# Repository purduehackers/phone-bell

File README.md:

# Phone Bell

A tool to turn a Western Electric rotary phone into a doorbell for Hack Night

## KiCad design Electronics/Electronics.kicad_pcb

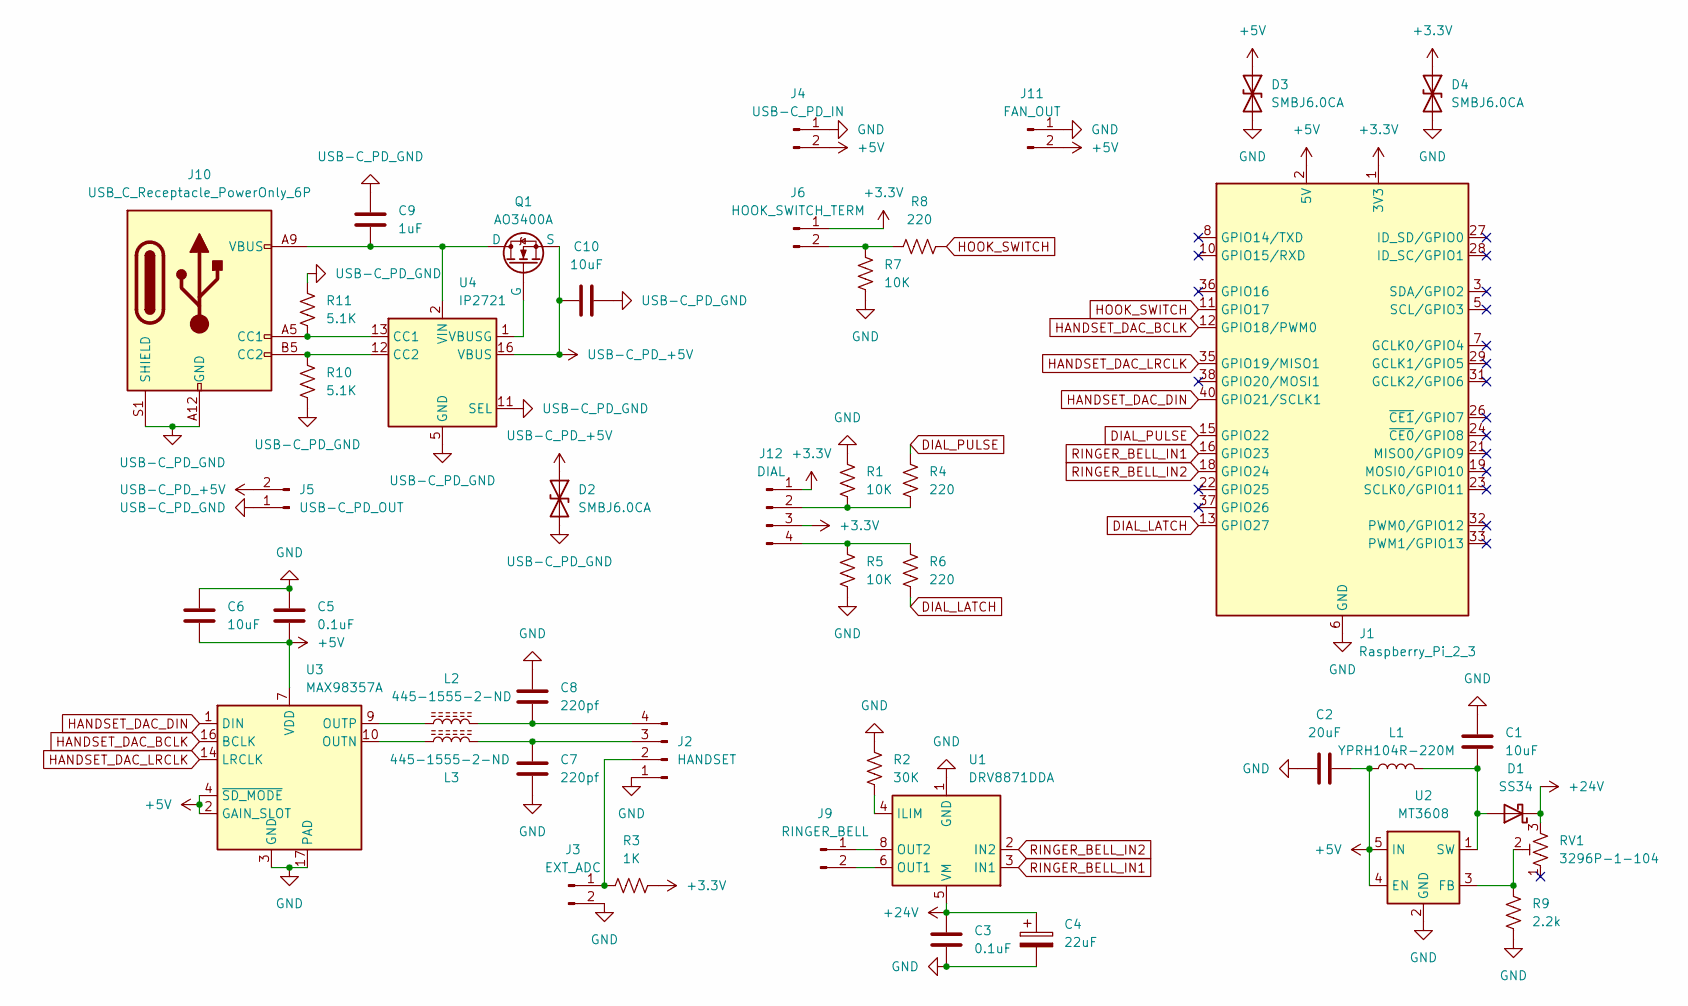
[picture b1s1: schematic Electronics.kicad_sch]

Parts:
C1, C6, C10: 10uF; C_0603_1608Metric
C2: 20uF; C_0603_1608Metric
C3, C5: 0.1uF; C_0603_1608Metric
C4: 22uF; C_0603_1608Metric
C7, C8: 220pf; C_0603_1608Metric
C9: 1uF; C_0603_1608Metric
D1: SS34; D_SMA
D2, D3, D4: SMBJ6.0CA; D_SMB
J1: Raspberry_Pi_2_3; PinSocket_2x20_P2.54mm_Vertical
J2: HANDSET; JST_XH_B4B-XH-A_1x04_P2.50mm_Vertical
J3: EXT_ADC; JST_XH_B2B-XH-A_1x02_P2.50mm_Vertical
J4: USB-C_PD_IN; JST_XH_B2B-XH-A_1x02_P2.50mm_Vertical
J5: USB-C_PD_OUT; JST_XH_B2B-XH-A_1x02_P2.50mm_Vertical
J6: HOOK_SWITCH_TERM; JST_XH_B2B-XH-A_1x02_P2.50mm_Vertical
J9: RINGER_BELL; JST_XH_B2B-XH-A_1x02_P2.50mm_Vertical
J10: USB_C_Receptacle_PowerOnly_6P; YIYUAN YTC-TC6-465
J11: FAN_OUT; PinHeader_1x02_P2.54mm_Vertical
J12: DIAL; JST_XH_B4B-XH-A_1x04_P2.50mm_Vertical
L1: YPRH104R-220M
L2, L3: 445-1555-2-ND; C_0805_2012Metric
Q1: AO3400A; SOT-23
R1, R5, R7: 10K; R_0603_1608Metric
R2: 30K; R_0603_1608Metric
R3: 1K; R_0603_1608Metric
R4, R6, R8: 220; R_0603_1608Metric
R9: 2.2k; R_0603_1608Metric
R10, R11: 5.1K; R_0603_1608Metric
RV1: 3296P-1-104; Potentiometer_Bourns_3296P_Horizontal
U1: DRV8871DDA; Texas_HTSOP-8-1EP_3.9x4.9mm_P1.27mm_EP2.95x4.9mm_Mask2.4x3.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
U2: MT3608; SOT-23-6
U3: MAX98357A; TQFN-16-1EP_3x3mm_P0.5mm_EP1.23x1.23mm
U4: IP2721; TSSOP-16_4.4x5mm_P0.65mm

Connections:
+3.3V: D4.1 (A1), J1.1 (3V3), J1.17 (3V3), J6.1, J12.1, J12.3, R3.1
+5V: C2.1, C5.2, C6.2, D3.1 (A1), J1.2 (5V), J1.4 (5V), J4.2, J11.2, L1.1, U2.4 (EN), U2.5 (IN), U3.2 (GAIN_SLOT), U3.4 (~SD_MODE), U3.7 (VDD), U3.8 (VDD)
+24V: C3.1, C4.1, D1.1 (K), RV1.3, U1.5 (VM)
DIAL_LATCH: J1.13 (GPIO27), R6.1
DIAL_PULSE: J1.15 (GPIO22), R4.1
GND: C1.2, C2.2, C3.2, C4.2, C5.1, C6.1, C7.2, C8.1, D3.2 (A2), D4.2 (A2), J1.6 (GND), J1.9 (GND), J1.14 (GND), J1.20 (GND), J1.25 (GND), J1.30 (GND), J1.34 (GND), J1.39 (GND), J2.1, J3.2, J4.1, J11.1, R1.1, R2.2, R5.1, R7.1, R9.1, U1.1 (GND), U1.7 (GND), U1.9 (GND), U2.2 (GND), U3.3 (GND), U3.11 (GND), U3.15 (GND), U3.17 (PAD)
HANDSET_DAC_BCLK: J1.12 (GPIO18/PWM0), U3.16 (BCLK)
HANDSET_DAC_DIN: J1.40 (GPIO21/SCLK1), U3.1 (DIN)
HANDSET_DAC_LRCLK: J1.35 (GPIO19/MISO1), U3.14 (LRCLK)
HOOK_SWITCH: J1.11 (GPIO17), R8.1
unnamed: C1.1, D1.2 (A), L1.2, U2.1 (SW)
unnamed: J2.2, J3.1, R3.2
unnamed: C7.1, J2.3, L3.2
unnamed: C8.2, J2.4, L2.2
unnamed: J6.2, R7.2, R8.2
unnamed: J9.1, U1.8 (OUT2)
unnamed: J9.2, U1.6 (OUT1)
unnamed: J10.A5 (CC1), R11.1, U4.13 (CC1)
unnamed: J10.B5 (CC2), R10.2, U4.12 (CC2)
unnamed: J12.2, R1.2, R4.2
unnamed: J12.4, R5.2, R6.2
unnamed: C9.2, J10.A9 (VBUS), J10.B9 (VBUS), Q1.1 (D), U4.2 (VIN)
unnamed: Q1.2 (G), U4.1 (VBUSG)
unnamed: R2.1, U1.4 (ILIM)
unnamed: R9.2, RV1.2, U2.3 (FB)
unnamed: L3.1, U3.10 (OUTN)
unnamed: L2.1, U3.9 (OUTP)
RINGER_BELL_IN1: J1.16 (GPIO23), U1.3 (IN1)
RINGER_BELL_IN2: J1.18 (GPIO24), U1.2 (IN2)
USB-C_PD_+5V: C10.1, D2.1 (A1), J5.2, Q1.3 (S), U4.16 (VBUS)
USB-C_PD_GND: C9.1, C10.2, D2.2 (A2), J5.1, J10.A12 (GND), J10.B12 (GND), J10.S1 (SHIELD), R10.1, R11.2, U4.5 (GND), U4.11 (SEL)

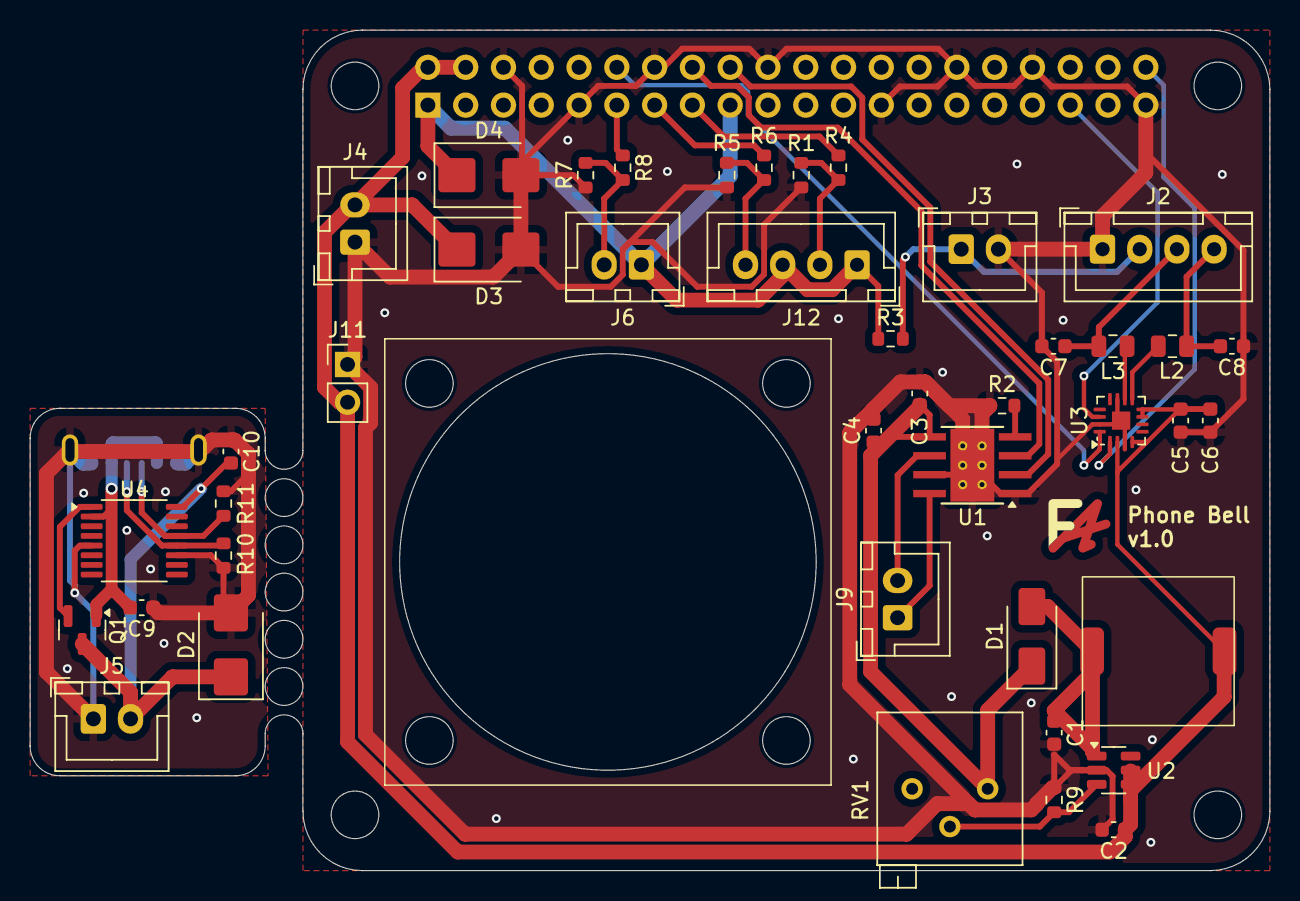
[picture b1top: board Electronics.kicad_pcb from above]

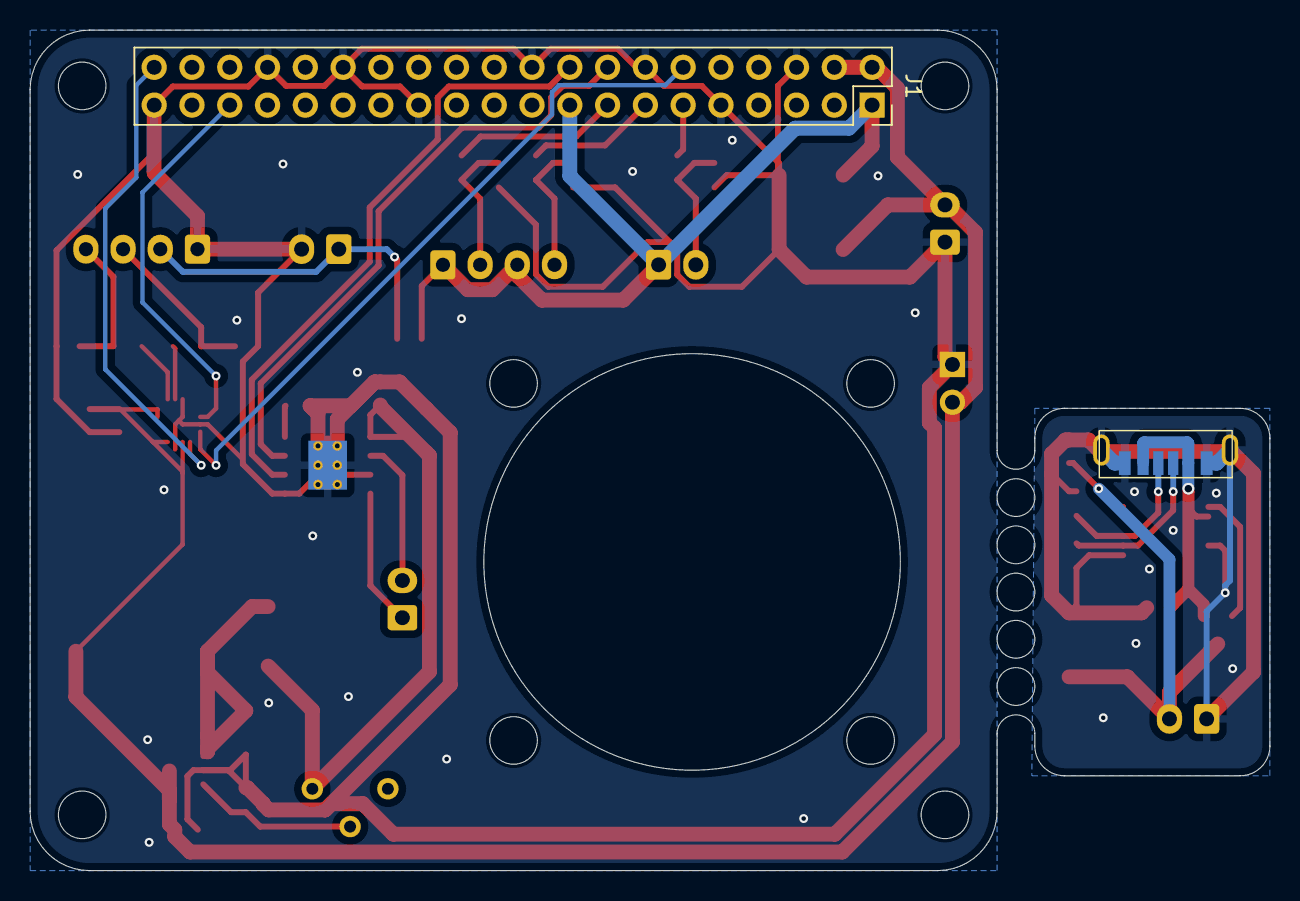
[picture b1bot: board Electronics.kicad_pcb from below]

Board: 2 copper layers, 83.3 x 56.5 mm, 44 parts (2 on the bottom side), 31 nets.

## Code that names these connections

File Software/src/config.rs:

pub const HOOK_SWITCH_PIN: u8 = 17;

pub const DIAL_LATCH_PIN: u8 = 22;
pub const DIAL_PULSE_PIN: u8 = 27;

pub const BELL_SOLENOID_FORWARD_PIN: u8 = 24;
pub const BELL_SOLENOID_REVERSE_PIN: u8 = 23;

/// How long (in seconds) the phone rings before giving up and playing the off-hook tone.
pub const RING_TIMEOUT_SECS: u64 = 30;

pub const KNOWN_NUMBERS: [&str; 7] = [
    "0",                                               // Operator
    "7",                                               // Test Number
    "349",                                             // "Fiz"
    "4225",                                            // "Hack"
    "34643664",                                        // "Dingdong",
    "8675309",                                         // the funny
    "47932786463439686262438634258447455587853896846", // "I swear to god if you manage to dial this ill just let you in"
];

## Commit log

2024-07-09 Threw together the preliminary logic for handling the IO for the phone
2024-07-09 Updated nativeBuildInputs in the nix shell
2024-07-09 Add panic handling inside the hardware initialization
2024-07-10 add some debug logging
2024-07-10 update hardware configuration to match wiring
2024-07-10 IO logic level fixes and allowing dialing to be reenabled
2024-07-10 trying the debouncr library instead of capacitors
2024-07-11 Increase debouncr debounce time
2024-07-11 Enforce a delay of at least 1ms between gpio reads
2024-07-11 Reduce the debouncr delay again lol
2024-07-11 Oops, forgot some reset logic, adding some debug info to ensure it's good!
2024-07-11 Oops, I think I reversed some time-delta logic
2024-07-12 Update UI defaults, add additional hardware debug messages, and change some electrical configuration parameters
2024-07-12 Update solenoid driver state writing code
2024-07-12 Create Initial KiCAD schematics and add a funny phone number to the config
2024-07-23 Added code to ring the bell properly through a DRV8871
2024-07-24 Populated the PCB schematic with the components from the final prototype. Preparting for a massive software push.
2024-08-01 V1 schematic and PCB are laid out and ready for production
2024-08-02 Finalized production exports and now awaiting PCBs to arrive
2024-08-13 Updated USB-C port on PCB, made test emulator for validating functionality.
2024-10-14 Added systemd service to the repository for repeated deployment purposes
2024-10-14 Added USB-C port holder model for the phone to the repository
2024-10-15 ported my emulator to the hardware abstraction layer for integration testing
2024-10-25 software is like 98% done, i just need to set up opus encoding/decoding for webrtc
2024-10-25 fuck it im just gonna make it ring the mf doorbell womp womp
2024-10-26 Made code work
2024-10-26 Audio has been marshaled but I don't wanna deal with mixing rn, I will do this later. -FizzyApple12
2024-11-07 Updated more WebRTC code and added some temporary sound making code as well as a direct web request to ring the doorbell
2024-11-09 Added silent dial number
2024-11-09 Fixed impl, added Docker
2024-11-09 updated volumes of audio files and added a test tone for the dial tester
2024-12-08 V1 firmware done
2024-12-08 please work, i'm begging you
2024-12-08 fixed incorrect remote peer setup order of operations
2025-02-06 fixed audio muting delay
2025-02-06 Fix clippy warnings
2025-02-06 updated systemd unit
2025-02-07 improved error messages in the audio subsystem
2025-02-07 here's an alsa config that works, don't suffer alone!
2025-02-07 better alsa config using device names
2026-01-31 rewrite for iroh
2026-01-31 docker for pi build
2026-02-02 refactor: use proper Docker build outputs
2026-02-02 ci: add GH Actions workflow to build binaries
2026-02-07 initial working state
2026-02-07 phone bell works now
2026-02-07 cleanup
2026-02-08 i fucked up merge
2026-02-28 remove doorbell calls
2026-03-06 hopefully fix dial on hook
2026-03-07 add ring timeout, hopefully fix audio
2026-03-08 small bug fixes for audio chopppiness
2026-03-28 claude slop
2026-03-28 door open
2026-04-11 more fix
